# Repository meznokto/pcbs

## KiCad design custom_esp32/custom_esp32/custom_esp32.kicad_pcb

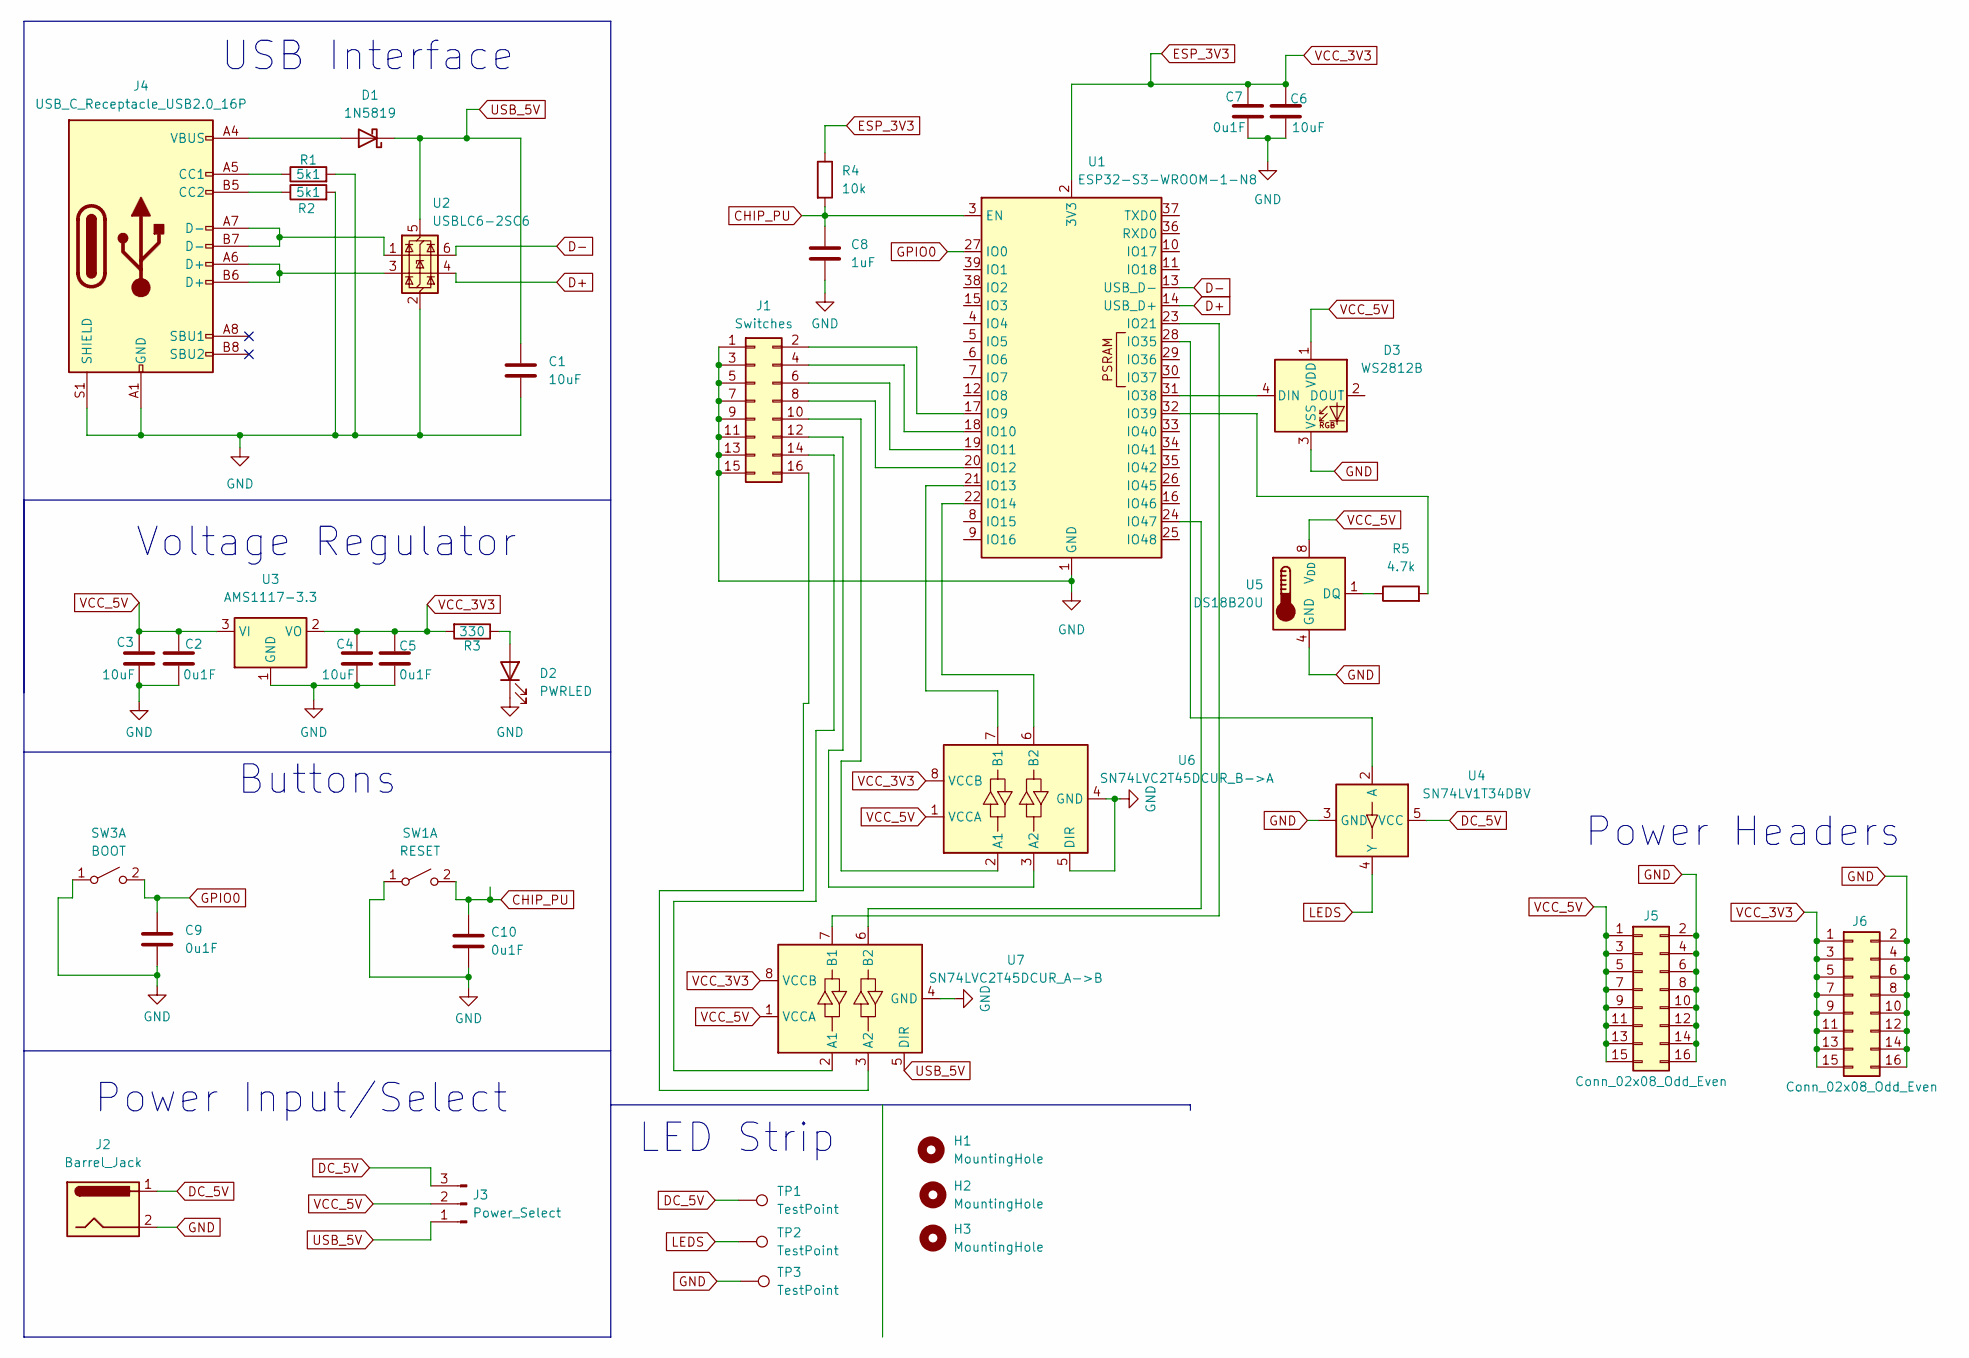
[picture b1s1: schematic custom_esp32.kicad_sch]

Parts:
C1, C3, C4: 10uF; C_0603_1608Metric; LCSC C19702
C2, C5, C9, C10: 0u1F; C_0603_1608Metric; LCSC C14663
C6: 10uF; LCSC C23186
C7: 0u1F; LCSC C1525
C8: 1uF; C_0603_1608Metric; LCSC C1592
D1: 1N5819; D_SOD-123; LCSC C82544
D2: PWRLED; LED_0603_1608Metric; LCSC C2286
D3: WS2812B; LED_WS2812B_PLCC4_5.0x5.0mm_P3.2mm; LCSC C2761795
H1, H2, H3: MountingHole; MountingHole_3.2mm_M3
J1: Switches; PinHeader_2x08_P2.54mm_Vertical; LCSC C61915
J2: Barrel_Jack; SolderWire-0.75sqmm_1x02_P7mm_D1.25mm_OD3.5mm
J3: Power_Select; PinHeader_1x03_P2.54mm_Vertical; LCSC C306127
J4: USB_C_Receptacle_USB2.0_16P; USB_C_Receptacle_GCT_USB4105-xx-A_16P_TopMnt_Horizontal; LCSC C2765186
J5, J6: Conn_02x08_Odd_Even; PinHeader_2x08_P2.54mm_Vertical
R1, R2: 5k1; R_0603_1608Metric; LCSC C23186
R3: 330; R_0805_2012Metric; LCSC C17630
R4: 10k; R_1206_3216Metric; LCSC C1489
R5: 4.7k; R_1206_3216Metric; LCSC C17936
SW1: RESET; SW_SPST_PTS645; LCSC C221871
SW3: BOOT; SW_SPST_PTS645; LCSC C221871
TP1, TP2, TP3: TestPoint; TestPoint_Pad_4.0x4.0mm
U1: ESP32-S3-WROOM-1-N8; ESP32-S3-WROOM-1; LCSC C2913198
U2: USBLC6-2SC6; SOT-23-6; LCSC C7519
U3: AMS1117-3.3; SOT-223-3_TabPin2; LCSC C6186
U4: SN74LV1T34DBV; SOT-23-5; LCSC C100024
U5: DS18B20U; MSOP-8_3x3mm_P0.65mm; LCSC C695836
U6: SN74LVC2T45DCUR_B->A; VSSOP-8_2.3x2mm_P0.5mm; LCSC C15741
U7: SN74LVC2T45DCUR_A->B; VSSOP-8_2.3x2mm_P0.5mm; LCSC C15741

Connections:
CHIP_PU: C8.1, C10.1, R4.2, SW1.2 (B), U1.3 (EN)
D+: U1.14 (USB_D+), U2.4 (I/O2)
D-: U1.13 (USB_D-), U2.6 (I/O1)
DC_5V: J2.1, J3.3, TP1.1, U4.5 (VCC)
ESP_3V3: C4.1, C5.1, C6.1, C7.1, J6.1, J6.3, J6.5, J6.7, J6.9, J6.11, J6.13, J6.15, R3.2, R4.1, U1.2 (3V3), U3.2 (VO), U6.8 (VCCB), U7.8 (VCCB)
GND: C1.2, C2.2, C3.2, C4.2, C5.2, C6.2, C7.2, C8.2, C9.2, C10.2, D2.1 (K), D3.3 (VSS), J1.1, J1.3, J1.5, J1.7, J1.9, J1.11, J1.13, J1.15, J2.2, J4.A1 (GND), J4.A12 (GND), J4.B1 (GND), J4.B12 (GND), J4.S1 (SHIELD), J5.2, J5.4, J5.6, J5.8, J5.10, J5.12, J5.14, J5.16, J6.2, J6.4, J6.6, J6.8, J6.10, J6.12, J6.14, J6.16, R1.2, R2.2, SW1.1 (A), SW3.1 (A), TP3.1, U1.1 (GND), U1.40 (GND), U1.41 (GND), U2.2 (GND), U3.1 (GND), U4.3 (GND), U5.4 (GND), U6.4 (GND), U6.5 (DIR), U7.4 (GND)
GPIO0: C9.1, SW3.2 (B), U1.27 (IO0)
LEDS: TP2.1, U4.4 (Y)
unnamed: D1.2 (A), J4.A4 (VBUS), J4.A9 (VBUS), J4.B4 (VBUS), J4.B9 (VBUS)
unnamed: D2.2 (A), R3.1
unnamed: D3.4 (DIN), U1.31 (IO38)
unnamed: J1.2, U1.17 (IO9)
unnamed: J1.4, U1.18 (IO10)
unnamed: J1.6, U1.19 (IO11)
unnamed: J1.8, U1.20 (IO12)
unnamed: J1.10, U6.2 (A1)
unnamed: J1.12, U6.3 (A2)
unnamed: J1.14, U7.2 (A1)
unnamed: J1.16, U7.3 (A2)
unnamed: J4.A5 (CC1), R1.1
unnamed: J4.B5 (CC2), R2.1
unnamed: J4.A6 (D+), J4.B6 (D+), U2.3 (I/O2)
unnamed: J4.A7 (D-), J4.B7 (D-), U2.1 (I/O1)
unnamed: U1.21 (IO13), U6.7 (B1)
unnamed: U1.22 (IO14), U6.6 (B2)
unnamed: U1.23 (IO21), U7.7 (B1)
unnamed: U1.28 (IO35), U4.2 (A)
unnamed: R5.2, U1.32 (IO39)
unnamed: U1.24 (IO47), U7.6 (B2)
unnamed: R5.1, U5.1 (DQ)
USB_5V: C1.1, D1.1 (K), J3.1, U2.5 (VBUS), U7.5 (DIR)
VCC_5V: C2.1, C3.1, D3.1 (VDD), J3.2, J5.1, J5.3, J5.5, J5.7, J5.9, J5.11, J5.13, J5.15, U3.3 (VI), U5.8 (V_{DD}), U6.1 (VCCA), U7.1 (VCCA)

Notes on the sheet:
Power Headers
Power Input/Select
USB Interface
Buttons
Voltage Regulator
LED Strip

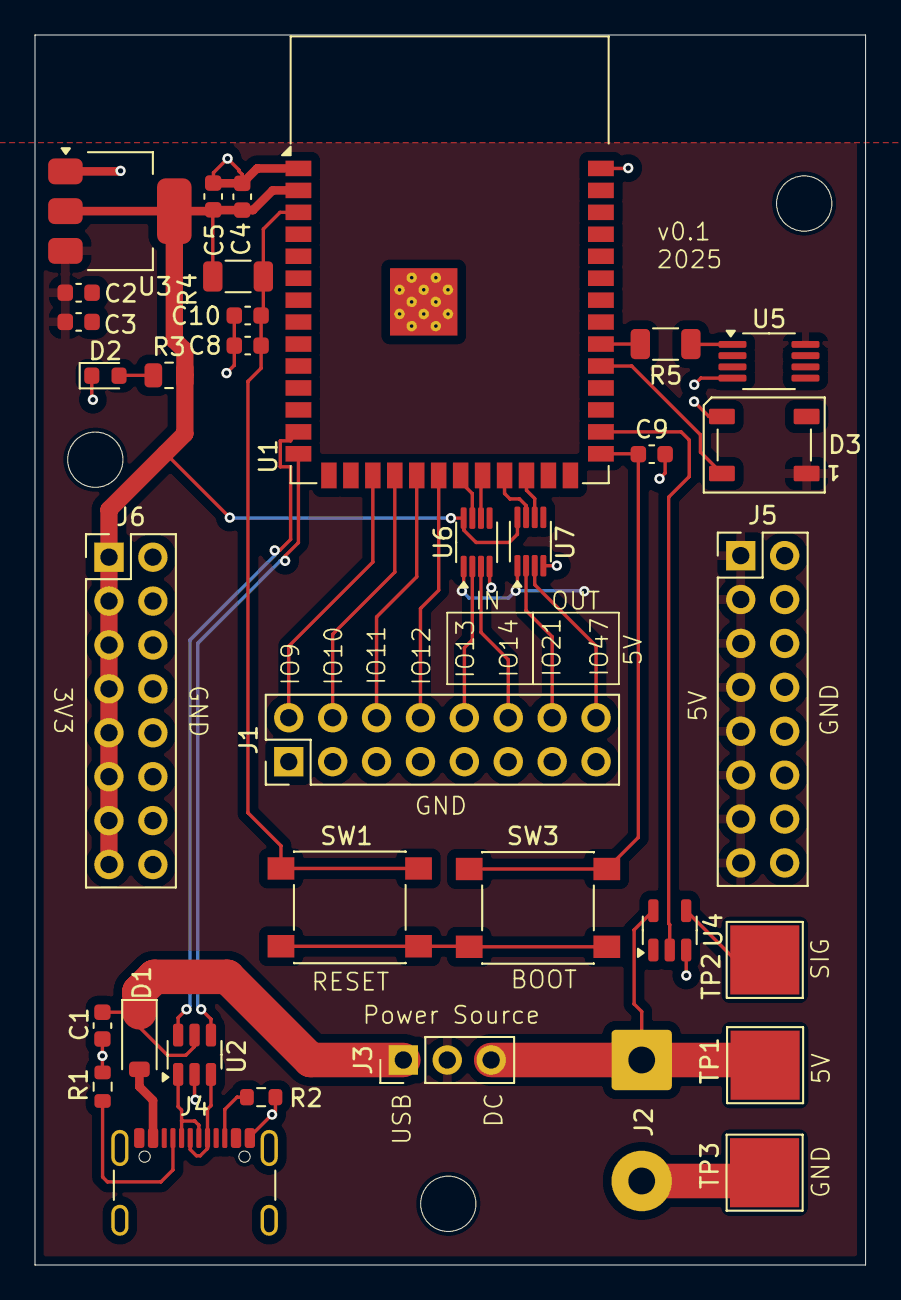
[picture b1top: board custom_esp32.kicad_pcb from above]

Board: 2 copper layers, 48.0 x 71.2 mm, 37 parts (0 on the bottom side), 32 nets.

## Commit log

2025-12-06 Initial commit.
2025-12-06 Added esp dev/led board.
2025-12-06 Added images for custom_esp32 pcb.
2025-12-19 Added picture of finished board.
